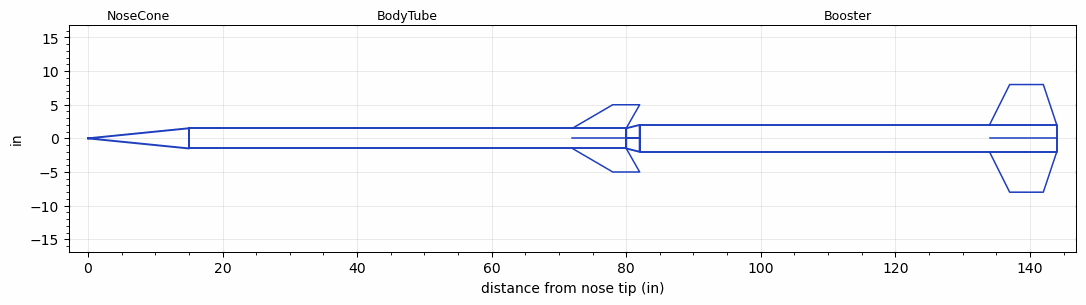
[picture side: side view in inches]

<RASAeroDocument>
 <FileVersion>2</FileVersion>
 <RocketDesign>
  <NoseCone>
   <Length>15</Length>
   <Diameter>3</Diameter>
   <Shape>Conical</Shape>
   <Location>0</Location>
  </NoseCone>
  <BodyTube>
   <Length>65</Length>
   <Diameter>3</Diameter>
   <Location>15</Location>
   <Fin>
    <Count>4</Count>
    <Chord>8</Chord>
    <Span>3.5</Span>
    <SweepDistance>6</SweepDistance>
    <TipChord>4</TipChord>
    <Thickness>0.187</Thickness>
    <LERadius>0.01</LERadius>
    <Location>8</Location>
    <AirfoilSection>Hexagonal</AirfoilSection>
    <FX1>0.75</FX1>
    <FX3>0.75</FX3>
   </Fin>
  </BodyTube>
  <Booster>
   <Length>62</Length>
   <Diameter>4</Diameter>
   <InsideDiameter>3</InsideDiameter>
   <Location>80</Location>
   <ShoulderLength>2</ShoulderLength>
   <Fin>
    <Count>4</Count>
    <Chord>10</Chord>
    <Span>6</Span>
    <SweepDistance>3</SweepDistance>
    <TipChord>5</TipChord>
    <Thickness>0.187</Thickness>
    <LERadius>0.01</LERadius>
    <Location>10</Location>
    <AirfoilSection>Hexagonal</AirfoilSection>
    <FX1>0.75</FX1>
    <FX3>0.75</FX3>
   </Fin>
  </Booster>
  <Surface>Rough Camouflage Paint</Surface>
  <ModifiedBarrowman>True</ModifiedBarrowman>
  <Turbulence>True</Turbulence>
  <UseBooster1>False</UseBooster1>
  <UseBooster2>False</UseBooster2>
 </RocketDesign>
 <LaunchSite>
  <Altitude>3700</Altitude>
  <Pressure>29.92</Pressure>
  <RodAngle>5</RodAngle>
  <RodLength>20</RodLength>
  <Temperature>80</Temperature>
  <WindSpeed>5</WindSpeed>
 </LaunchSite>
 <Recovery>
  <Altitude1>1000</Altitude1>
  <Altitude2>1000</Altitude2>
  <DeviceType1>Parachute</DeviceType1>
  <DeviceType2>None</DeviceType2>
  <Event1>True</Event1>
  <Event2>False</Event2>
  <Size1>8</Size1>
  <Size2>1</Size2>
  <EventType1>Apogee</EventType1>
  <EventType2>None</EventType2>
  <CD1>1</CD1>
  <CD2>1.33</CD2>
 </Recovery>
 <SimulationList>
  <Simulation>
   <SustainerEngine>3in-N4118  (TsKrush)</SustainerEngine>
   <SustainerLaunchWt>26</SustainerLaunchWt>
   <SustainerNozzleDiameter>2.9</SustainerNozzleDiameter>
   <SustainerCG>50.48</SustainerCG>
   <SustainerIgnitionDelay>10</SustainerIgnitionDelay>
   <Booster1Engine>4in-RCS-O5808  (TsKrush)</Booster1Engine>
   <Booster1LaunchWt>62.9</Booster1LaunchWt>
   <Booster1SeparationDelay>0</Booster1SeparationDelay>
   <Booster1IgnitionDelay>0</Booster1IgnitionDelay>
   <Booster1CG>88</Booster1CG>
   <Booster1NozzleDiameter>3.8</Booster1NozzleDiameter>
   <IncludeBooster1>True</IncludeBooster1>
   <Booster2Delay>0</Booster2Delay>
   <IncludeBooster2>False</IncludeBooster2>
   <TimetoApogee>207.3978</TimetoApogee>
   <MaxAltitude>624493.4</MaxAltitude>
   <MaxVelocity>6840.867</MaxVelocity>
  </Simulation>
 </SimulationList>
</RASAeroDocument>
